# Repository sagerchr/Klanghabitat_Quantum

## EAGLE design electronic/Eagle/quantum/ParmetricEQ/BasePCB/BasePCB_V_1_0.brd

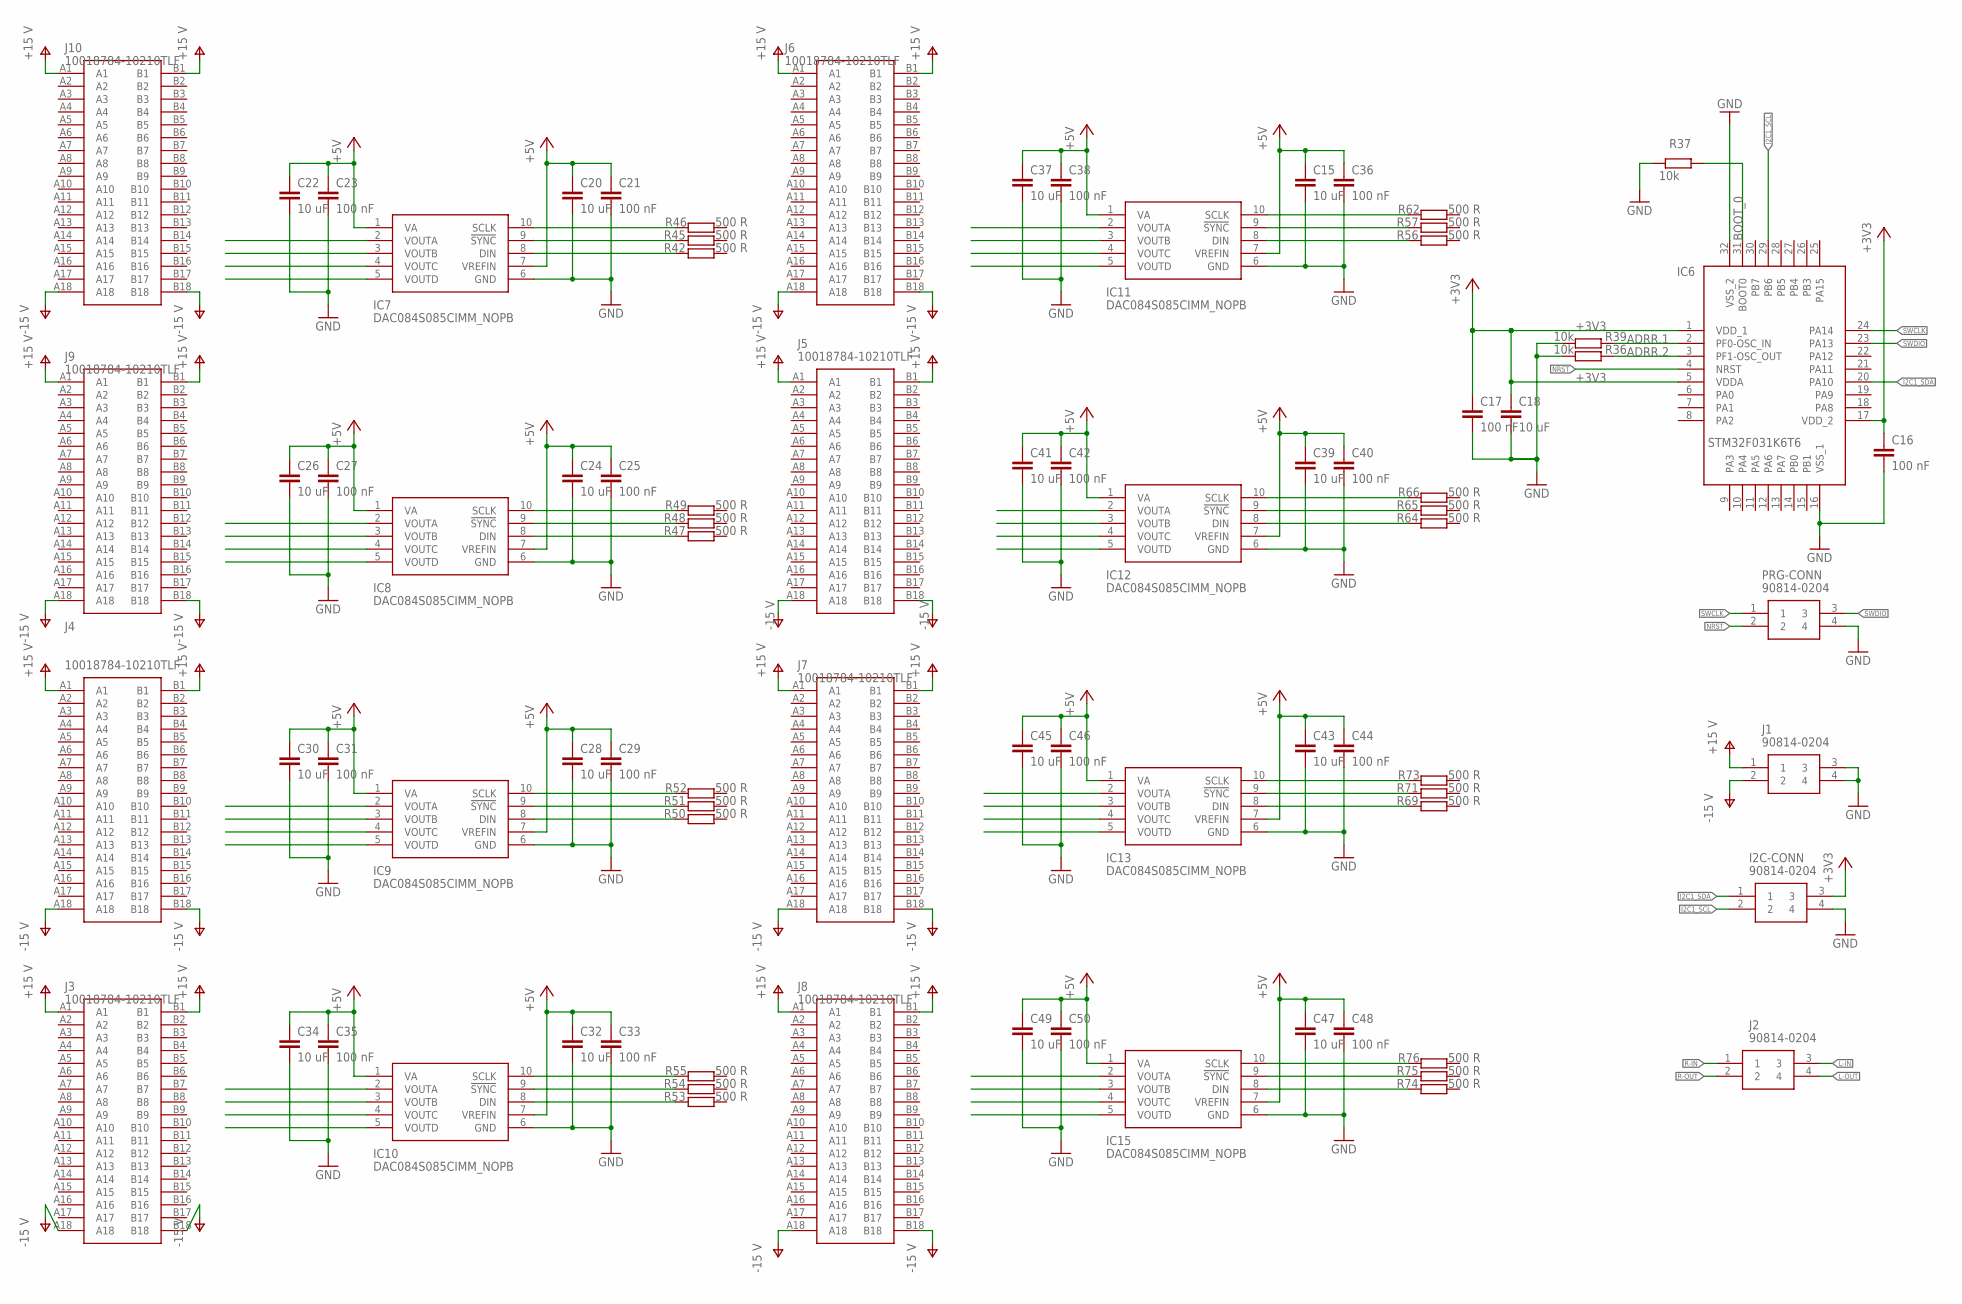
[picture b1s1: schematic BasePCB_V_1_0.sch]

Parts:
C15, C18, C20, C22, C24, C26, C28, C30, C32, C34, C37, C39, C41, C43, C45, C47, C49: 10 uF; C1206
C16, C17, C21, C23, C25, C27, C29, C31, C33, C35, C36, C38, C40, C42, C44, C46, C48, C50: 100 nF; C0603
I2C-CONN: 90814-0204; MOLEX_90814-0204
IC6: STM32F031K6T6; QFP80P900X900X160-32N
IC7, IC8, IC9, IC10, IC11, IC12, IC13, IC15: DAC084S085CIMM_NOPB; SOP50P490X110-10N
J1, J2: 90814-0204; MOLEX_90814-0204
J3, J4, J5, J6, J7, J8, J9, J10: 10018784-10210TLF; 1001878410210TLF
PRG-CONN: 90814-0204; MOLEX_90814-0204
R36, R37, R39: 10k; R0603
R42, R45, R46, R47, R48, R49, R50, R51, R52, R53, R54, R55, R56, R57, R62, R64, R65, R66, R69, R71, R73, R74, R75, R76: 500 R; R0603

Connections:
+3V3: C16.1, C17.1, C18.1, I2C-CONN.3, IC6.1 (VDD_1), IC6.5 (VDDA), IC6.17 (VDD_2)
+5V: C15.1, C20.1, C21.1, C22.1, C23.1, C24.1, C25.1, C26.1, C27.1, C28.1, C29.1, C30.1, C31.1, C32.1, C33.1, C34.1, C35.1, C36.1, C37.1, C38.1, C39.1, C40.1, C41.1, C42.1, C43.1, C44.1, C45.1, C46.1, C47.1, C48.1, C49.1, C50.1, IC7.1 (VA), IC7.7 (VREFIN), IC8.1 (VA), IC8.7 (VREFIN), IC9.1 (VA), IC9.7 (VREFIN), IC10.1 (VA), IC10.7 (VREFIN), IC11.1 (VA), IC11.7 (VREFIN), IC12.1 (VA), IC12.7 (VREFIN), IC13.1 (VA), IC13.7 (VREFIN), IC15.1 (VA), IC15.7 (VREFIN)
ADRR.1: IC6.2 (PF0-OSC_IN), R39.2
ADRR.2: IC6.3 (PF1-OSC_OUT), R36.2
BOOT_0: IC6.31 (BOOT0), R37.2
GND: C15.2, C16.2, C17.2, C18.2, C20.2, C21.2, C22.2, C23.2, C24.2, C25.2, C26.2, C27.2, C28.2, C29.2, C30.2, C31.2, C32.2, C33.2, C34.2, C35.2, C36.2, C37.2, C38.2, C39.2, C40.2, C41.2, C42.2, C43.2, C44.2, C45.2, C46.2, C47.2, C48.2, C49.2, C50.2, I2C-CONN.4, IC6.16 (VSS_1), IC6.32 (VSS_2), IC7.6 (GND), IC8.6 (GND), IC9.6 (GND), IC10.6 (GND), IC11.6 (GND), IC12.6 (GND), IC13.6 (GND), IC15.6 (GND), J1.3, J1.4, PRG-CONN.4, R36.1, R37.1, R39.1
I2C1_SCL: I2C-CONN.2, IC6.29 (PB6)
I2C1_SDA: I2C-CONN.1, IC6.20 (PA10)
L-IN: J2.3
L-OUT: J2.4
unnamed: IC7.8 (DIN), R42.1
unnamed: IC7.9 (!SYNC), R45.1
unnamed: IC7.10 (SCLK), R46.1
unnamed: IC8.8 (DIN), R47.1
unnamed: IC8.9 (!SYNC), R48.1
unnamed: IC8.10 (SCLK), R49.1
unnamed: IC9.8 (DIN), R50.1
unnamed: IC9.9 (!SYNC), R51.1
unnamed: IC9.10 (SCLK), R52.1
unnamed: IC10.8 (DIN), R53.1
unnamed: IC10.9 (!SYNC), R54.1
unnamed: IC10.10 (SCLK), R55.1
unnamed: IC11.8 (DIN), R56.1
unnamed: IC11.9 (!SYNC), R57.1
unnamed: IC11.10 (SCLK), R62.1
unnamed: IC12.8 (DIN), R64.1
unnamed: IC12.9 (!SYNC), R65.1
unnamed: IC12.10 (SCLK), R66.1
unnamed: IC13.8 (DIN), R69.1
unnamed: IC13.9 (!SYNC), R71.1
unnamed: IC13.10 (SCLK), R73.1
unnamed: IC15.8 (DIN), R74.1
unnamed: IC15.9 (!SYNC), R75.1
unnamed: IC15.10 (SCLK), R76.1
NRST: IC6.4 (NRST), PRG-CONN.2
R-IN: J2.1
R-OUT: J2.2
SWCLK: IC6.24 (PA14), PRG-CONN.1
SWDIO: IC6.23 (PA13), PRG-CONN.3
V+: J1.1, J3.A1, J3.B1, J4.A1, J4.B1, J5.A1, J5.B1, J6.A1, J6.B1, J7.A1, J7.B1, J8.A1, J8.B1, J9.A1, J9.B1, J10.A1, J10.B1
V-: J1.2, J3.A18, J4.A18, J5.A18, J6.A18, J7.A18, J8.A18, J9.A18, J10.A18, J10.B18

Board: 2 copper layers, 83 parts (0 on the bottom side), 37 nets, no tracks yet.

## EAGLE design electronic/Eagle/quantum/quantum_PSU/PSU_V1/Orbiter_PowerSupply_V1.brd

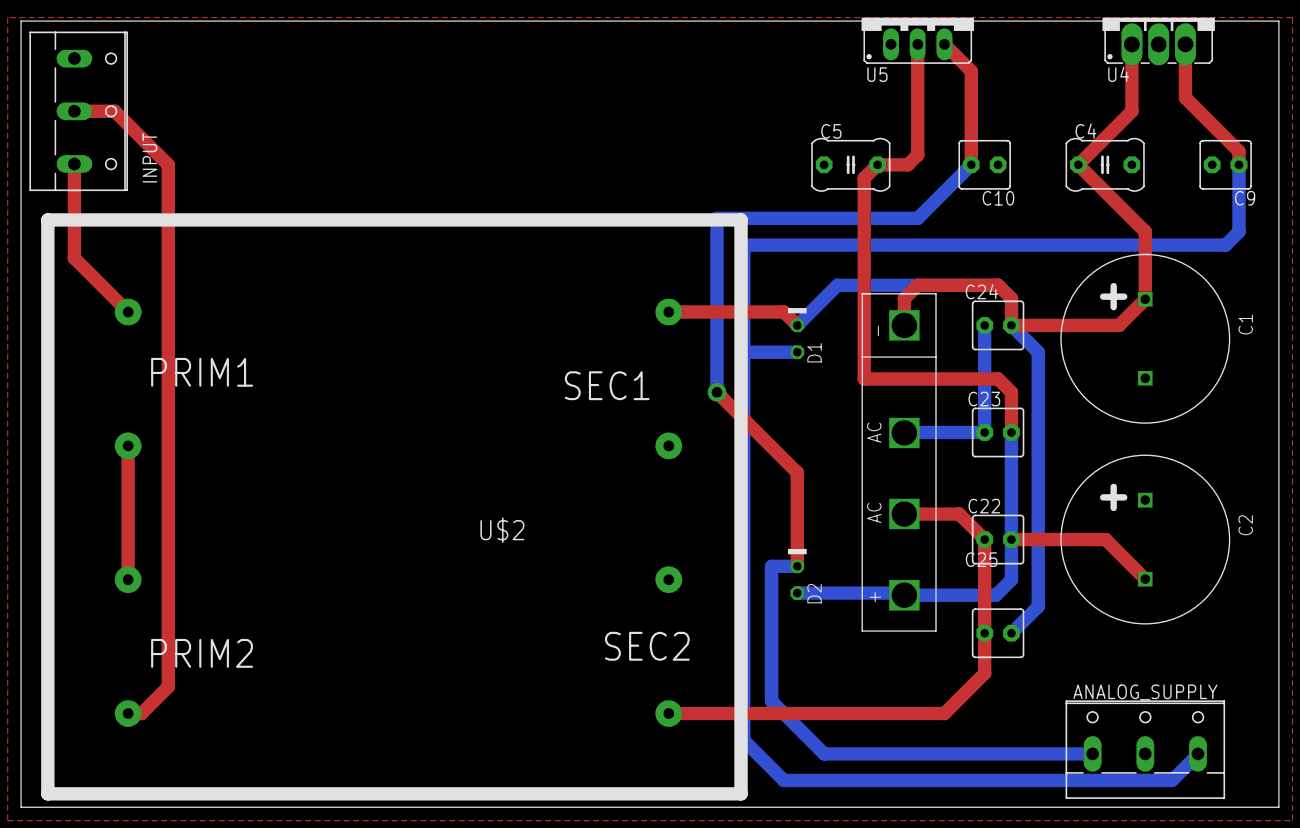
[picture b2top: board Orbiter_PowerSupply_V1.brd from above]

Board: 2 copper layers, 119.4 x 74.6 mm, 18 parts (0 on the bottom side), 10 nets.

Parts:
ANALOG_SUPPLY: Analog_Supply; W237-103
C1, C2: 4700µF; ELECTROLYTIC_16MM
C4, C5: 0,3 µF; C5MM
C9, C10: 100nF; C2.5MM
C22, C23, C24, C25: 10nF; C2.5MM
D1, D2: 4148THT; D-5
INPUT: Mains Supply; W237-103
U4: 7815; 78XXS_
U5: 7915; 79XXS
U$1: GLEICHRICHTER; SIL_RECTIFER
U$2: PRINTTRAFO_30-600-LPI

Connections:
+15V: ANALOG_SUPPLY.3, C9.1, D1.A, U4.OUT
-15V: ANALOG_SUPPLY.1, C10.2, D2.C, U5.OUT
A_GND: ANALOG_SUPPLY.2, C1.-, C2.+, C4.2, C5.1, C9.2, C10.1, U4.GND, U5.GND, U$2.6, U$2.8
unnamed: INPUT.3, U$2.3
unnamed: INPUT.2, U$2.1
unnamed: C23.1, C24.2, U$1.AC1
unnamed: C1.+, C4.1, C24.1, C25.1, D1.C, U4.IN, U$1.+, U$2.7
unnamed: C22.1, C25.2, U$1.AC2, U$2.5
unnamed: U$2.2, U$2.4
unnamed: C2.-, C5.2, C22.2, C23.2, D2.A, U5.IN, U$1.-

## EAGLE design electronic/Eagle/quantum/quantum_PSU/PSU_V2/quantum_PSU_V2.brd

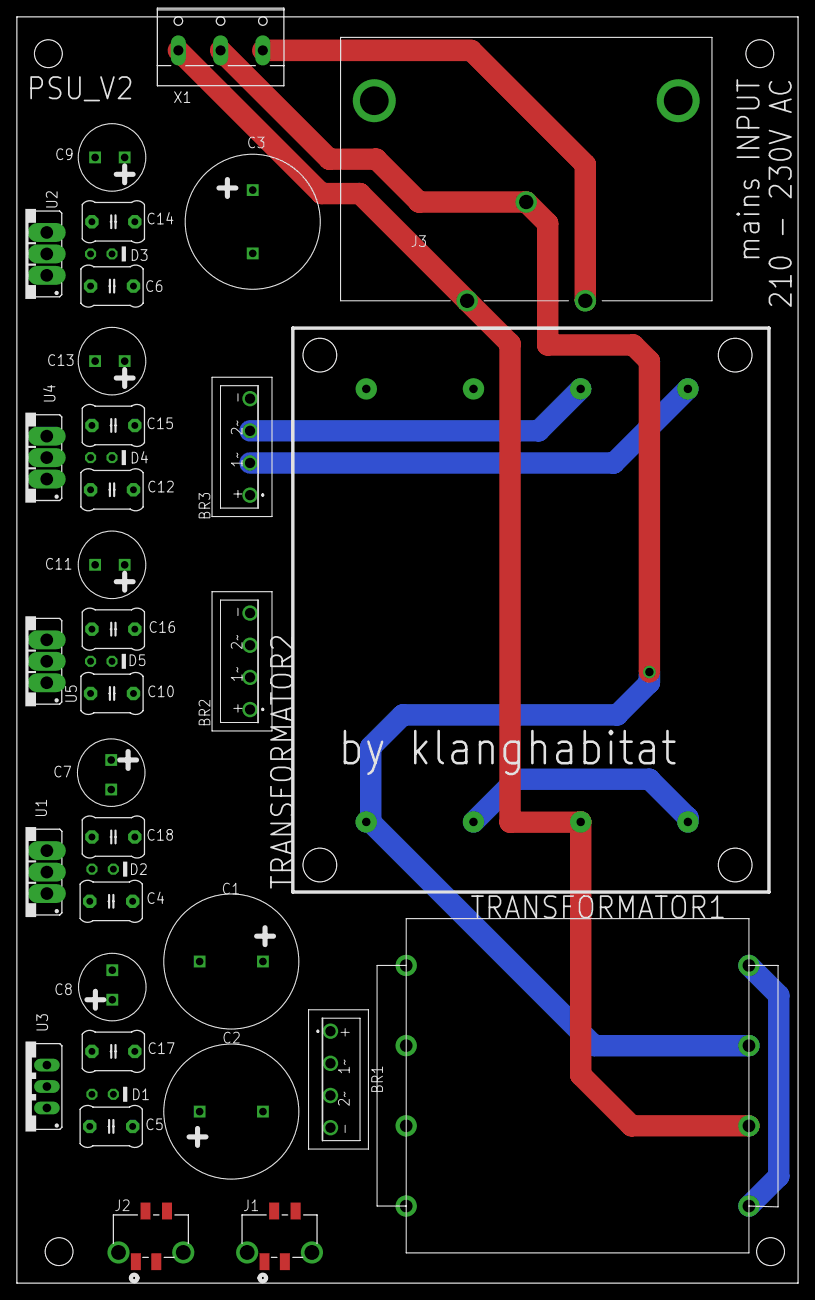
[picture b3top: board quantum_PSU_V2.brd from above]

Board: 2 copper layers, 92.5 x 150.0 mm, 37 parts (0 on the bottom side), 19 nets.

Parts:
BR1, BR2, BR3: BRIDGE_RECTIFIER; KBP308G
C1, C3: 4700 uF/25 V; ELECTROLYTIC_16MM
C2: 4700 uF/25V; ELECTROLYTIC_16MM
C4, C5, C6, C10, C12, C14, C15, C16, C17, C18: 100 nF; C5MM
C7, C8, C9, C11, C13: 100 uF/25V; ELECTROLYTIC_8MM
D1, D2, D3, D4, D5: 4148; DIODE_THT_STANDING
J1, J2: 90814-0204; MOLEX_90814-0204
J3: PF0030_PC; PF0030PC
TRANSFORMATOR1: PRINTTRAFO2X15@0.4A_SIZE6; LP_SIZE_6
TRANSFORMATOR2: PRINTTRAFO2X15V@1.2A_SIZE18; LPI_SIZE_18
U1: 7815; 78XXS_
U2: 7812; 78XXS_
U3: 7915; 79XXS
U4: 7805; 78XXS_
U5: LD1117AV33; 78XXS_
X1: W237-103

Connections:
+3V3_OUT: C13.+, C16.1, D5.A, J2.1, U5.OUT
+5V_OUT: C11.+, C15.1, D4.A, J2.4, U4.OUT
+12V_OUT: C9.+, C14.1, D3.A, J2.2, U2.OUT
+15V_OUT: C7.+, C18.1, D2.A, J1.1, U1.OUT
-15V_OUT: C8.-, C17.2, D1.C, J1.2, U3.OUT
AGND: C1.-, C2.+, C4.2, C5.1, C7.-, C8.+, C17.1, C18.2, J1.3, J1.4, TRANSFORMATOR1.P$5, TRANSFORMATOR1.P$8, U1.GND, U3.GND
CHASSIS: J3.2, X1.3
DGND: BR2.4, BR3.4, C3.-, C6.2, C9.-, C10.2, C11.-, C12.2, C13.-, C14.2, C15.2, C16.2, J2.3, U2.GND, U4.GND, U5.GND
unnamed: BR2.1, BR3.1, C3.+, C6.1, C10.1, C12.1, D3.C, D4.C, D5.C, U2.IN, U4.IN, U5.IN
unnamed: BR1.3, TRANSFORMATOR1.P$6
unnamed: TRANSFORMATOR1.P$1, TRANSFORMATOR1.P$4
unnamed: TRANSFORMATOR2.P$1, TRANSFORMATOR2.P$4
unnamed: BR3.3, TRANSFORMATOR2.P$6
unnamed: J3.3, TRANSFORMATOR1.P$3, TRANSFORMATOR2.P$3, X1.2
unnamed: J3.1, TRANSFORMATOR1.P$2, TRANSFORMATOR2.P$2, X1.1
unnamed: BR3.2, TRANSFORMATOR2.P$5
unnamed: BR1.2, TRANSFORMATOR1.P$7
unnamed: BR1.1, C1.+, C4.1, D2.C, U1.IN
unnamed: BR1.4, C2.-, C5.2, D1.A, U3.IN

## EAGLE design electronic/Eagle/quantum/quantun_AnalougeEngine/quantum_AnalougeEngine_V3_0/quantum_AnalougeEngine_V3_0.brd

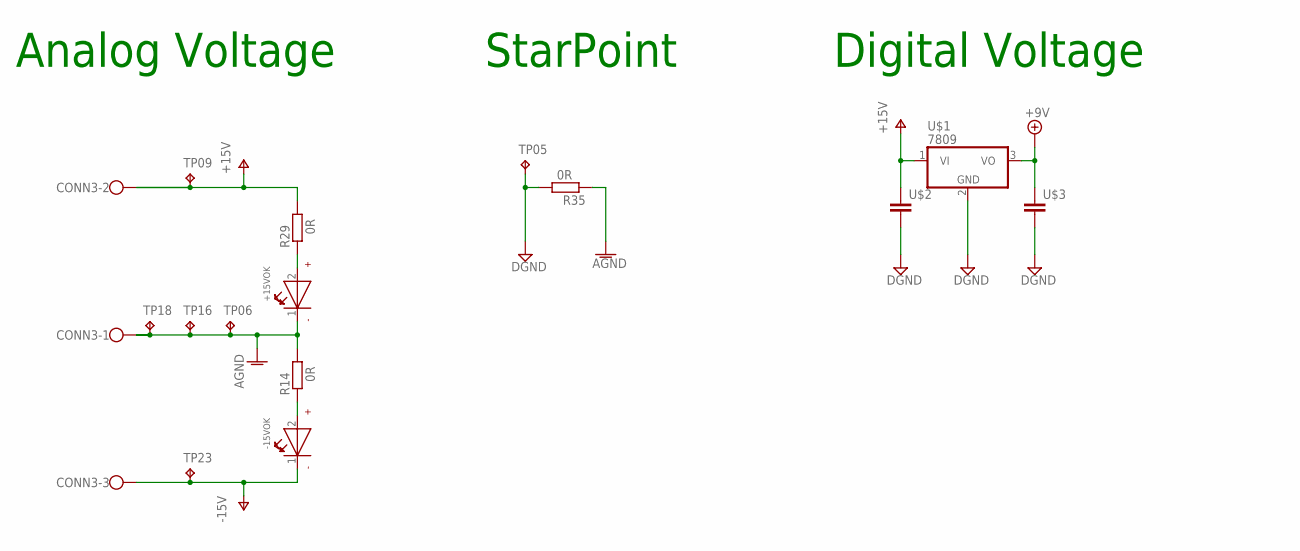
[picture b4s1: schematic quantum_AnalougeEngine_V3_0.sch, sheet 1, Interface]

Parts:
+15VOK: SMD_LED_0603; WL-SMCW_0603
-15VOK: SMD_LED_0603; WL-SMCW_0603
CONN3: SCHRAUBKLEMME_3POL; W237-103
R14, R29, R35: 0R; R0805
TP05, TP06, TP09, TP16, TP18, TP23: TPTHT; THT_PIN
U$1: 7809; TO252
U$2, U$3: CAPACITOR"; C0603

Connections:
+9V: U$1.3 (VO), U$3.1; also elsewhere on the board
AGND: +15VOK.1 (-), CONN3.1, R14.2, R35.1, TP06.P$1, TP16.P$1, TP18.P$1; also elsewhere on the board
DGND: R35.2, TP05.P$1, U$1.2 (GND), U$2.2, U$3.2; also elsewhere on the board
unnamed: -15VOK.2 (+), R14.1
unnamed: +15VOK.2 (+), R29.1
V+: CONN3.2, R29.2, TP09.P$1, U$1.1 (VI), U$2.1; also elsewhere on the board
V-: -15VOK.1 (-), CONN3.3, TP23.P$1; also elsewhere on the board

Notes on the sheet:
StarPoint
Analog Voltage
Digital Voltage

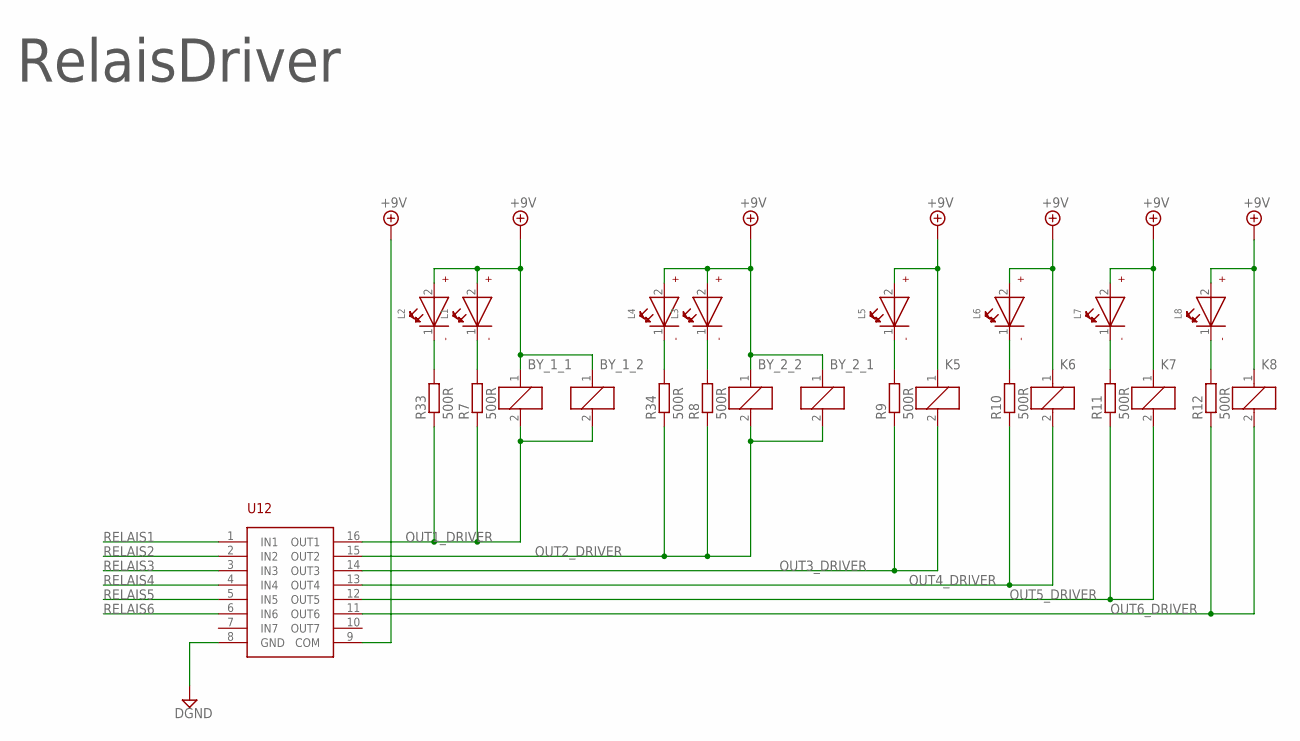
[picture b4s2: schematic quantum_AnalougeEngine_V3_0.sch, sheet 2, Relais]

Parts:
BY_1_1, BY_1_2, BY_2_1, BY_2_2: RELAY_EE2-5NU; 351
K5, K6, K7, K8: RELAY_EE2-5NU; 351
L1, L2, L3, L4, L5, L6, L7, L8: SMD_LED_0603; WL-SMCW_0603
R7, R8, R9, R10, R11, R12, R33, R34: 500R; R0805
U12: ULN2003; SOIC16

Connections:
+9V: BY_1_1.1, BY_1_2.1, BY_2_1.1, BY_2_2.1, K5.1, K6.1, K7.1, K8.1, L1.2 (+), L2.2 (+), L3.2 (+), L4.2 (+), L5.2 (+), L6.2 (+), L7.2 (+), L8.2 (+), U12.9 (COM); also elsewhere on the board
DGND: U12.8 (GND); also elsewhere on the board
unnamed: L1.1 (-), R7.2
unnamed: L3.1 (-), R8.2
unnamed: L8.1 (-), R12.2
unnamed: L7.1 (-), R11.2
unnamed: L6.1 (-), R10.2
unnamed: L5.1 (-), R9.2
unnamed: L2.1 (-), R33.2
unnamed: L4.1 (-), R34.2
OUT1_DRIVER: BY_1_1.2, BY_1_2.2, R7.1, R33.1, U12.16 (OUT1)
OUT2_DRIVER: BY_2_1.2, BY_2_2.2, R8.1, R34.1, U12.15 (OUT2)
OUT3_DRIVER: K5.2, R9.1, U12.14 (OUT3)
OUT4_DRIVER: K6.2, R10.1, U12.13 (OUT4)
OUT5_DRIVER: K7.2, R11.1, U12.12 (OUT5)
OUT6_DRIVER: K8.2, R12.1, U12.11 (OUT6)
RELAIS1: U12.1 (IN1); also elsewhere on the board
RELAIS2: U12.2 (IN2); also elsewhere on the board
RELAIS3: U12.3 (IN3); also elsewhere on the board
RELAIS4: U12.4 (IN4); also elsewhere on the board
RELAIS5: U12.5 (IN5); also elsewhere on the board
RELAIS6: U12.6 (IN6); also elsewhere on the board

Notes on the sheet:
RelaisDriver

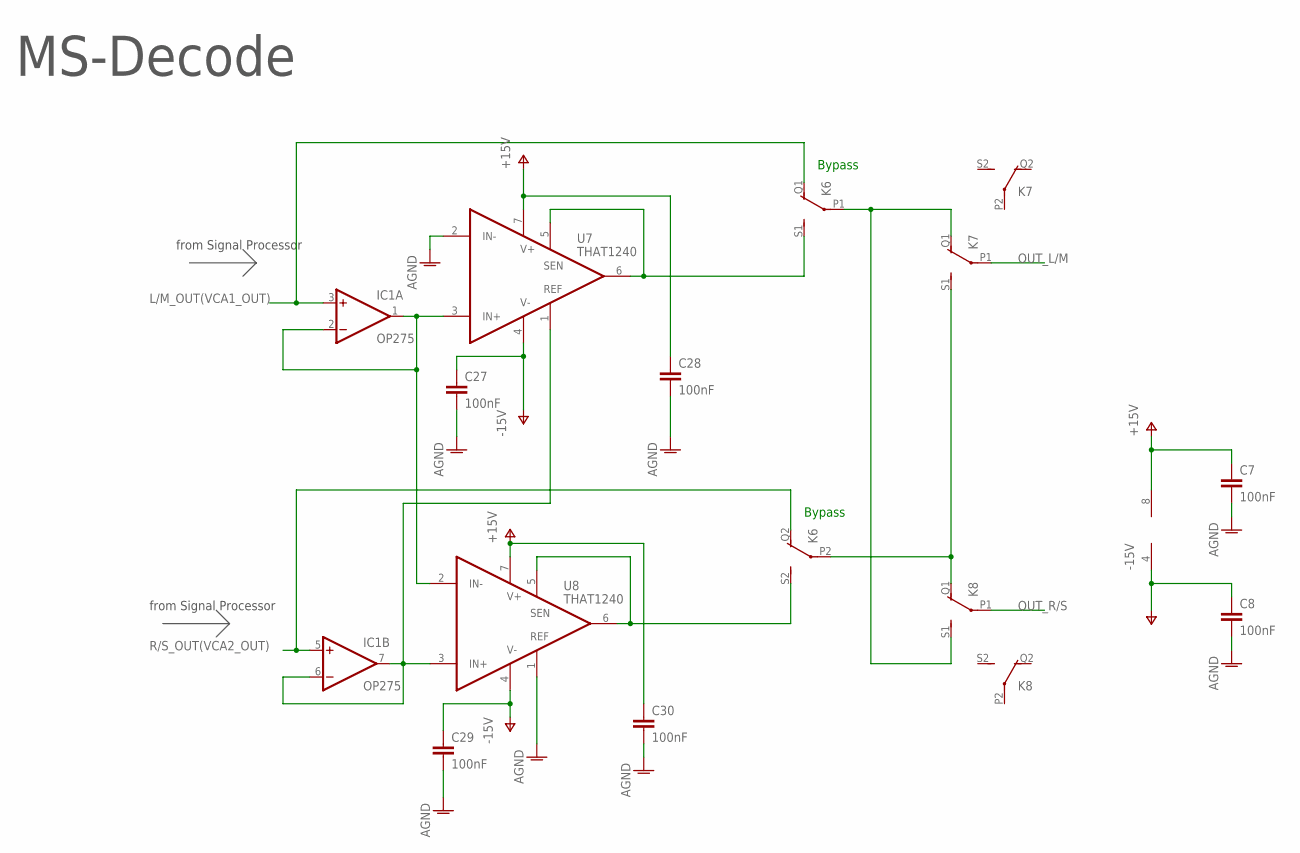
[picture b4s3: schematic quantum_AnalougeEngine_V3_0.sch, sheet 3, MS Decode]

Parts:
C7, C8, C27, C28, C29, C30: 100nF; C0603
IC1: OP275; SOIC8
K6, K7, K8: RELAY_EE2-5NU; 351
U7, U8: THAT1240; SO08

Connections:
AGND: C7.2, C8.2, C27.2, C28.2, C29.2, C30.2, U7.2 (IN-), U8.1 (REF); also elsewhere on the board
L/M_OUT(VCA1_OUT): IC1.3 (+IN), K6.Q1 (O); also elsewhere on the board
M1: K6.S1 (S), U7.5 (SEN), U7.6 (OUT)
unnamed: K6.P1, K7.Q1 (O), K8.S1 (S)
unnamed: K6.P2, K7.S1 (S), K8.Q1 (O)
unnamed: IC1.6 (-IN), IC1.7 (OUT), U7.1 (REF), U8.3 (IN+)
unnamed: IC1.1 (OUT), IC1.2 (-IN), U7.3 (IN+), U8.2 (IN-)
OUT_L/M: K7.P1; also elsewhere on the board
OUT_R/S: K8.P1; also elsewhere on the board
R/S_OUT(VCA2_OUT): IC1.5 (+IN), K6.Q2 (O); also elsewhere on the board
S1: K6.S2 (S), U8.5 (SEN), U8.6 (OUT)
V+: C7.1, C28.1, C30.1, IC1.8 (V+), U7.7 (V+), U8.7 (V+); also elsewhere on the board
V-: C8.1, C27.1, C29.1, IC1.4 (V-), U7.4 (V-), U8.4 (V-); also elsewhere on the board

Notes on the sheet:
from Signal Processor
MS-Decode
Bypass

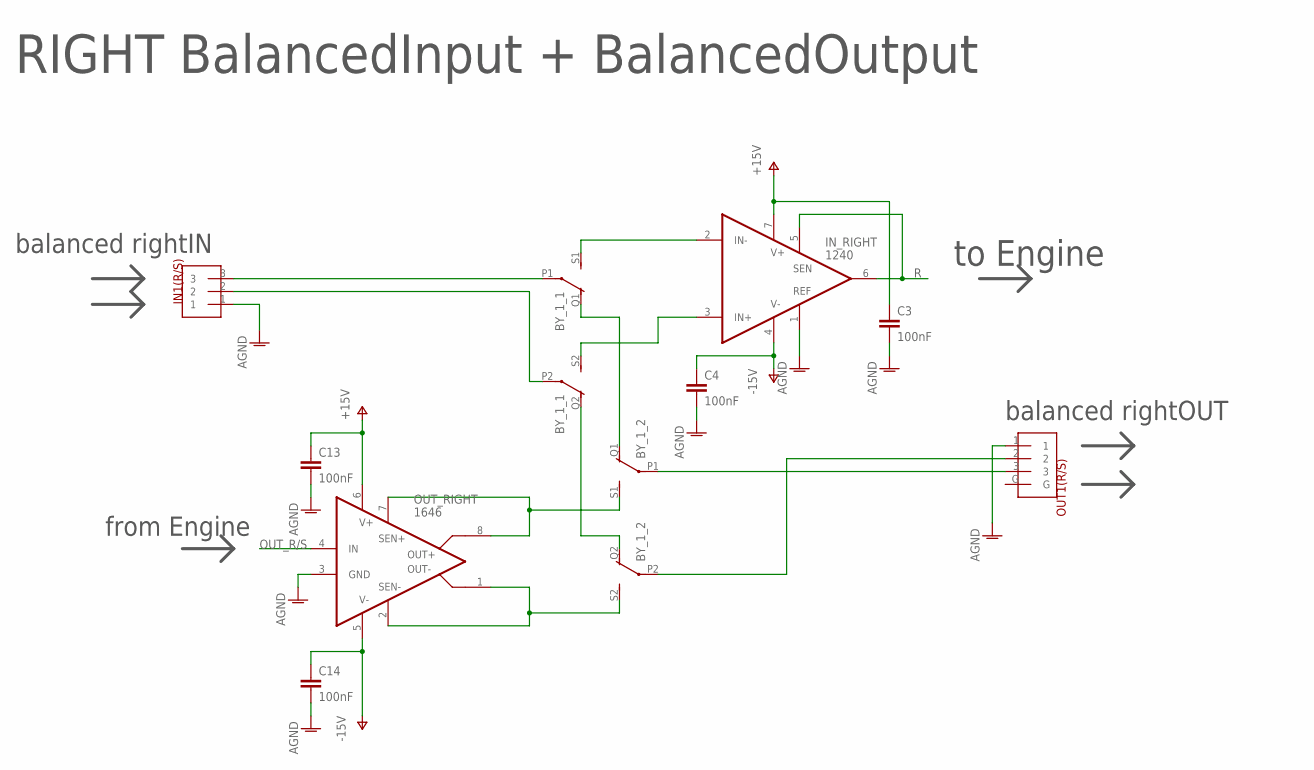
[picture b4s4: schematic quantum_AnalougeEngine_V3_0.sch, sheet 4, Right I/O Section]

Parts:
BY_1_1, BY_1_2: RELAY_EE2-5NU; 351
C3, C4, C13, C14: 100nF; C0603
IN1(R/S): NEUTRIK_NC3FAH
IN_RIGHT: 1240; SO08
OUT1(R/S): NEUTRIK_NC3MAH
OUT_RIGHT: 1646; SO08

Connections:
AGND: C3.2, C4.2, C13.2, C14.2, IN1(R/S).1, IN_RIGHT.1 (REF), OUT1(R/S).1, OUT_RIGHT.3 (GND); also elsewhere on the board
unnamed: BY_1_1.S1 (S), IN_RIGHT.2 (IN-)
unnamed: BY_1_1.S2 (S), IN_RIGHT.3 (IN+)
unnamed: BY_1_1.Q1 (O), BY_1_2.Q1 (O)
unnamed: BY_1_1.Q2 (O), BY_1_2.Q2 (O)
unnamed: BY_1_1.P2, IN1(R/S).2
unnamed: BY_1_1.P1, IN1(R/S).3
unnamed: BY_1_2.P2, OUT1(R/S).2
unnamed: BY_1_2.P1, OUT1(R/S).3
OUT_R/S: OUT_RIGHT.4 (IN); also elsewhere on the board
R: IN_RIGHT.5 (SEN), IN_RIGHT.6 (OUT); also elsewhere on the board
R/S_OUT+: BY_1_2.S1 (S), OUT_RIGHT.7 (SEN+), OUT_RIGHT.8 (OUT+)
R/S_OUT-: BY_1_2.S2 (S), OUT_RIGHT.1 (OUT-), OUT_RIGHT.2 (SEN-)
V+: C3.1, C13.1, IN_RIGHT.7 (V+), OUT_RIGHT.6 (V+); also elsewhere on the board
V-: C4.1, C14.1, IN_RIGHT.4 (V-), OUT_RIGHT.5 (V-); also elsewhere on the board

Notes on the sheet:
RIGHT BalancedInput + BalancedOutput
balanced rightIN
balanced rightOUT
from Engine
to Engine

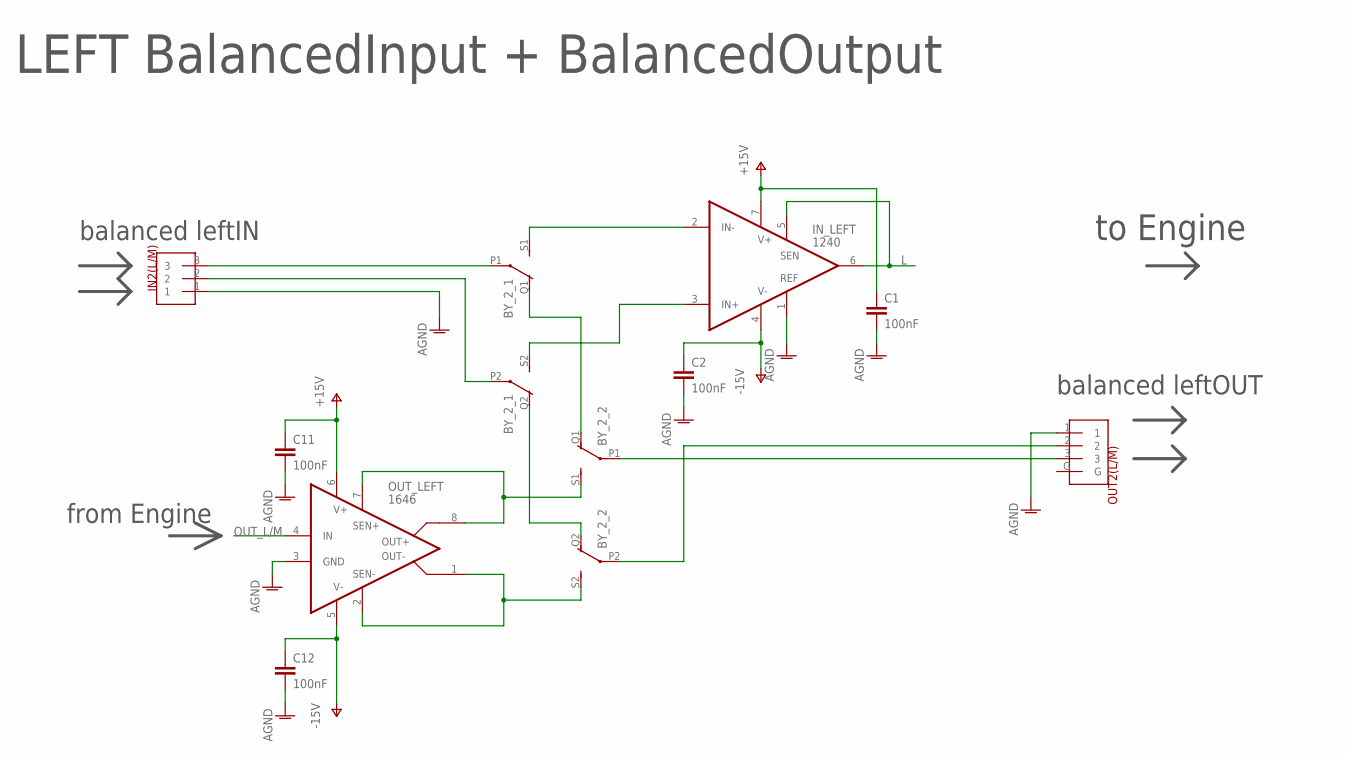
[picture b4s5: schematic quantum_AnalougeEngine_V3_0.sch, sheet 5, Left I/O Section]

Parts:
BY_2_1, BY_2_2: RELAY_EE2-5NU; 351
C1, C2, C11, C12: 100nF; C0603
IN2(L/M): NEUTRIK_NC3FAH
IN_LEFT: 1240; SO08
OUT2(L/M): NEUTRIK_NC3MAH
OUT_LEFT: 1646; SO08

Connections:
AGND: C1.2, C2.2, C11.2, C12.2, IN2(L/M).1, IN_LEFT.1 (REF), OUT2(L/M).1, OUT_LEFT.3 (GND); also elsewhere on the board
L: IN_LEFT.5 (SEN), IN_LEFT.6 (OUT); also elsewhere on the board
L/M_OUT+: BY_2_2.S1 (S), OUT_LEFT.7 (SEN+), OUT_LEFT.8 (OUT+)
L/M_OUT-: BY_2_2.S2 (S), OUT_LEFT.1 (OUT-), OUT_LEFT.2 (SEN-)
unnamed: BY_2_1.S2 (S), IN_LEFT.3 (IN+)
unnamed: BY_2_1.S1 (S), IN_LEFT.2 (IN-)
unnamed: BY_2_2.P1, OUT2(L/M).3
unnamed: BY_2_2.P2, OUT2(L/M).2
unnamed: BY_2_1.P1, IN2(L/M).3
unnamed: BY_2_1.P2, IN2(L/M).2
unnamed: BY_2_1.Q1 (O), BY_2_2.Q1 (O)
unnamed: BY_2_1.Q2 (O), BY_2_2.Q2 (O)
OUT_L/M: OUT_LEFT.4 (IN); also elsewhere on the board
V+: C1.1, C11.1, IN_LEFT.7 (V+), OUT_LEFT.6 (V+); also elsewhere on the board
V-: C2.1, C12.1, IN_LEFT.4 (V-), OUT_LEFT.5 (V-); also elsewhere on the board

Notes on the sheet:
balanced leftIN
balanced leftOUT
from Engine
to Engine
LEFT BalancedInput + BalancedOutput

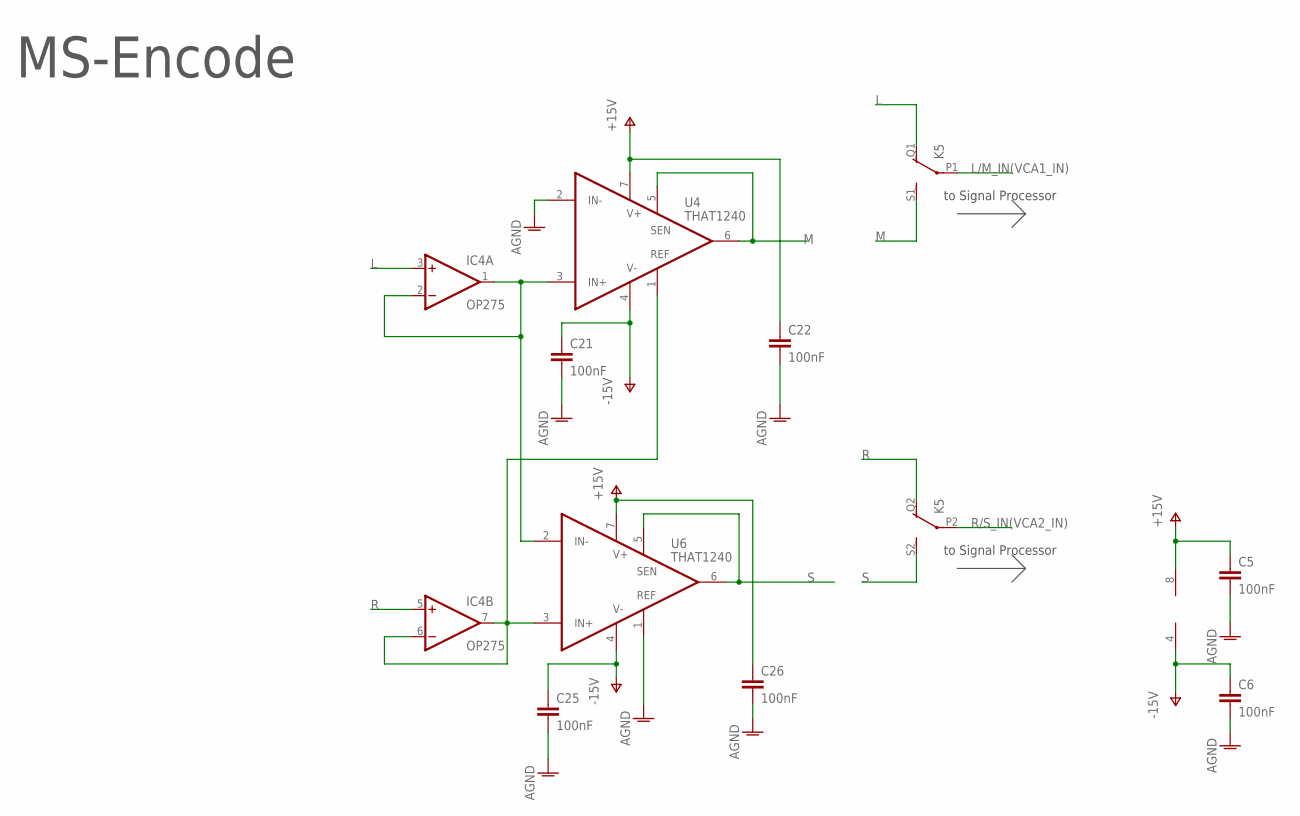
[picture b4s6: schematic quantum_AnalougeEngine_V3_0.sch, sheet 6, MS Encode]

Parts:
C5, C6, C21, C22, C25, C26: 100nF; C0603
IC4: OP275; SOIC8
K5: RELAY_EE2-5NU; 351
U4, U6: THAT1240; SO08

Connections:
AGND: C5.2, C6.2, C21.2, C22.2, C25.2, C26.2, U4.2 (IN-), U6.1 (REF); also elsewhere on the board
L: IC4.3 (+IN), K5.Q1 (O); also elsewhere on the board
L/M_IN(VCA1_IN): K5.P1; also elsewhere on the board
M: K5.S1 (S), U4.5 (SEN), U4.6 (OUT)
unnamed: IC4.1 (OUT), IC4.2 (-IN), U4.3 (IN+), U6.2 (IN-)
unnamed: IC4.6 (-IN), IC4.7 (OUT), U4.1 (REF), U6.3 (IN+)
R: IC4.5 (+IN), K5.Q2 (O); also elsewhere on the board
R/S_IN(VCA2_IN): K5.P2; also elsewhere on the board
S: K5.S2 (S), U6.5 (SEN), U6.6 (OUT)
V+: C5.1, C22.1, C26.1, IC4.8 (V+), U4.7 (V+), U6.7 (V+); also elsewhere on the board
V-: C6.1, C21.1, C25.1, IC4.4 (V-), U4.4 (V-), U6.4 (V-); also elsewhere on the board

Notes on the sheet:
to Signal Processor
MS-Encode

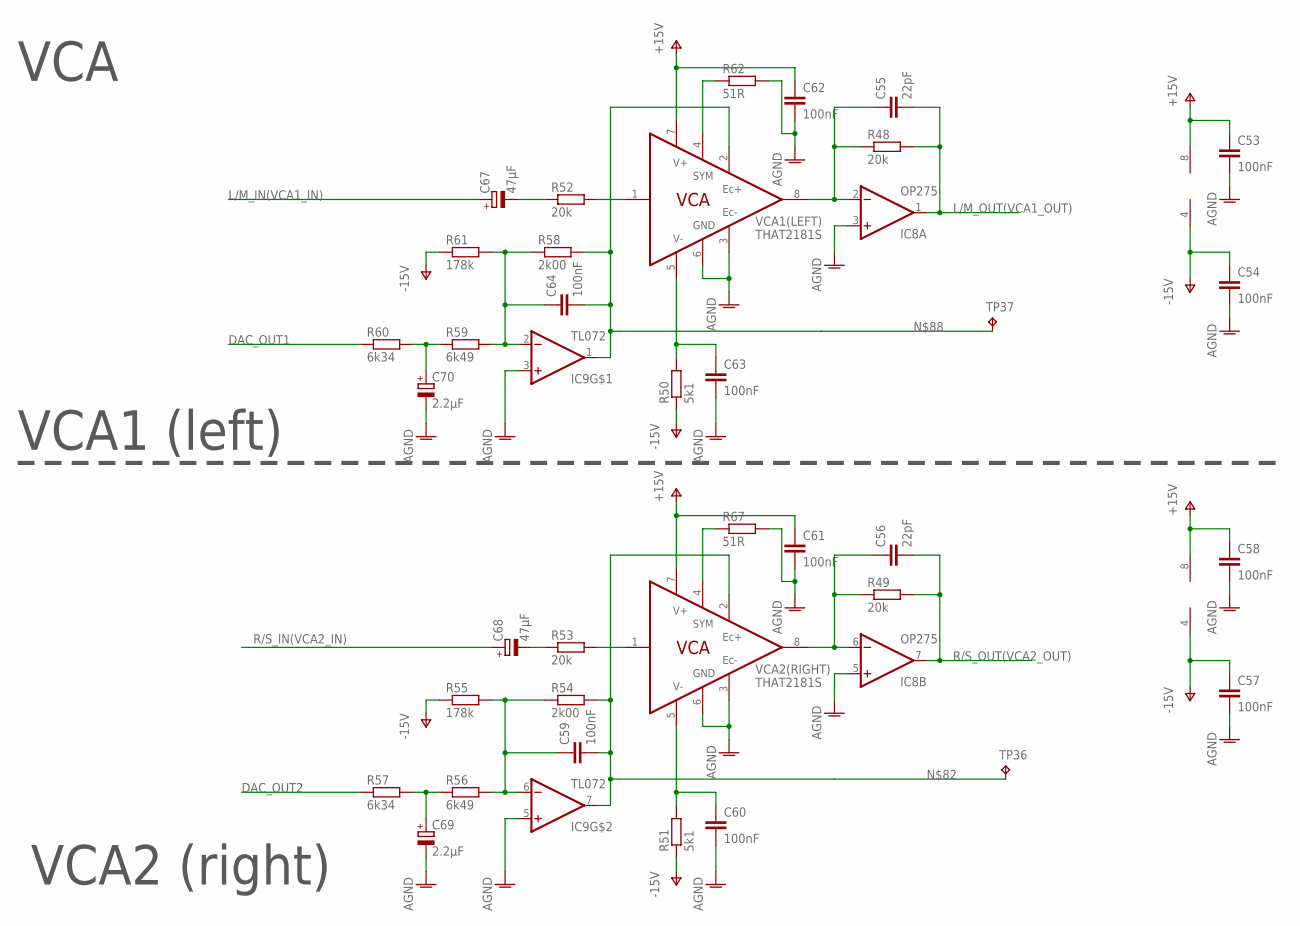
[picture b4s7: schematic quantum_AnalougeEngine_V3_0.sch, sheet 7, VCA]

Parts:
C53, C54, C57, C58, C59, C60, C61, C62, C63, C64: 100nF; C0603
C55, C56: 22pF; C0603
C67, C68: 47µF; 153CLV-0605
C69, C70: 2.2µF; 153CLV-0605
IC8: OP275; SOIC8
IC9: TL072; SOIC8
R48, R49, R52, R53: 20k; R0805
R50, R51: 5k1; R0805
R54, R58: 2k00; R0805
R55, R61: 178k; R0805
R56, R59: 6k49; R0805
R57, R60: 6k34; R0805
R62, R67: 51R; R0805
TP36, TP37: TPTHT; THT_PIN
VCA1(LEFT), VCA2(RIGHT): THAT2181S; SO08

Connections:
AGND: C53.2, C54.2, C57.2, C58.2, C60.2, C61.2, C62.2, C63.2, C69.-, C70.-, IC8.3 (+IN), IC8.5 (+IN), IC9.3 (+IN), IC9.5 (+IN), R62.2, R67.2, VCA1(LEFT).3 (EC-), VCA1(LEFT).6 (GND), VCA2(RIGHT).3 (EC-), VCA2(RIGHT).6 (GND); also elsewhere on the board
DAC_OUT1: R60.1; also elsewhere on the board
DAC_OUT2: R57.1; also elsewhere on the board
L/M_IN(VCA1_IN): C67.+; also elsewhere on the board
L/M_OUT(VCA1_OUT): C55.2, IC8.1 (OUT), R48.2; also elsewhere on the board
unnamed: C55.1, IC8.2 (-IN), R48.1, VCA1(LEFT).8 (OUT)
unnamed: R52.2, VCA1(LEFT).1 (IN)
unnamed: C67.-, R52.1
unnamed: C70.+, R59.1, R60.2
unnamed: C56.1, IC8.6 (-IN), R49.1, VCA2(RIGHT).8 (OUT)
unnamed: C60.1, R51.2, VCA2(RIGHT).5 (V-)
unnamed: C68.-, R53.1
unnamed: R53.2, VCA2(RIGHT).1 (IN)
unnamed: C63.1, R50.2, VCA1(LEFT).5 (V-)
unnamed: C59.1, IC9.6 (-IN), R54.1, R55.2, R56.2
unnamed: C59.2, IC9.7 (OUT), R54.2, TP36.P$1, VCA2(RIGHT).2 (EC+)
unnamed: C64.1, IC9.2 (-IN), R58.1, R59.2, R61.2
unnamed: C69.+, R56.1, R57.2
unnamed: R62.1, VCA1(LEFT).4 (SYM)
unnamed: C64.2, IC9.1 (OUT), R58.2, TP37.P$1, VCA1(LEFT).2 (EC+)
unnamed: R67.1, VCA2(RIGHT).4 (SYM)
R/S_IN(VCA2_IN): C68.+; also elsewhere on the board
R/S_OUT(VCA2_OUT): C56.2, IC8.7 (OUT), R49.2; also elsewhere on the board
V+: C53.1, C58.1, C61.1, C62.1, IC8.8 (V+), IC9.8 (V+), VCA1(LEFT).7 (V+), VCA2(RIGHT).7 (V+); also elsewhere on the board
V-: C54.1, C57.1, IC8.4 (V-), IC9.4 (V-), R50.1, R51.1, R55.1, R61.1; also elsewhere on the board

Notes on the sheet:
VCA
VCA1 (left)
VCA2 (right)

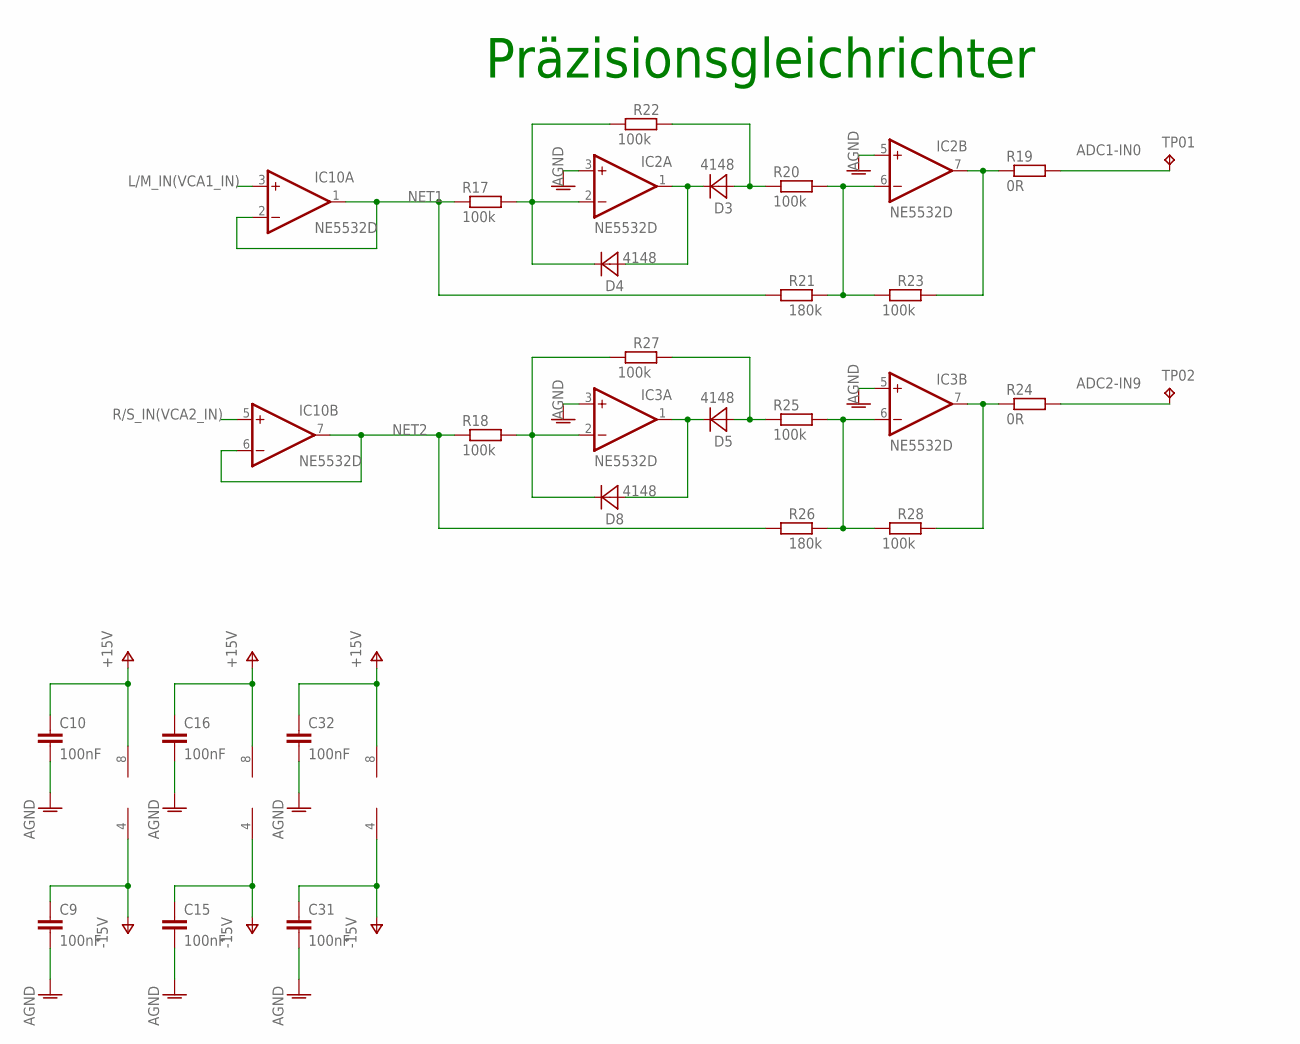
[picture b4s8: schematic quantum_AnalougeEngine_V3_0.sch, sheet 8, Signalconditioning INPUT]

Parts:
C9, C10, C15, C16, C31, C32: 100nF; C0603
D3, D4, D5, D8: 4148; SOD323-R
IC2, IC3, IC10: NE5532D; SO08
R17, R18, R20, R22, R23, R25, R27, R28: 100k; R0805
R19, R24: 0R; R0805
R21, R26: 180k; R0805
TP01, TP02: TPTHT; THT_PIN

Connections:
ADC1-IN0: R19.2, TP01.P$1; also elsewhere on the board
ADC2-IN9: R24.2, TP02.P$1; also elsewhere on the board
AGND: C9.2, C10.2, C15.2, C16.2, C31.2, C32.2, IC2.3 (+IN), IC2.5 (+IN), IC3.3 (+IN), IC3.5 (+IN); also elsewhere on the board
L/M_IN(VCA1_IN): IC10.3 (+IN); also elsewhere on the board
unnamed: D4.C, IC2.2 (-IN), R17.2, R22.1
unnamed: D3.C, D4.A, IC2.1 (OUT)
unnamed: D3.A, R20.1, R22.2
unnamed: IC2.6 (-IN), R20.2, R21.2, R23.1
unnamed: IC2.7 (OUT), R19.1, R23.2
unnamed: D8.C, IC3.2 (-IN), R18.2, R27.1
unnamed: D5.C, D8.A, IC3.1 (OUT)
unnamed: D5.A, R25.1, R27.2
unnamed: IC3.6 (-IN), R25.2, R26.2, R28.1
unnamed: IC3.7 (OUT), R24.1, R28.2
NET1: IC10.1 (OUT), IC10.2 (-IN), R17.1, R21.1
NET2: IC10.6 (-IN), IC10.7 (OUT), R18.1, R26.1
R/S_IN(VCA2_IN): IC10.5 (+IN); also elsewhere on the board
V+: C10.1, C16.1, C32.1, IC2.8 (V+), IC3.8 (V+), IC10.8 (V+); also elsewhere on the board
V-: C9.1, C15.1, C31.1, IC2.4 (V-), IC3.4 (V-), IC10.4 (V-); also elsewhere on the board

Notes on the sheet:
Präzisionsgleichrichter
